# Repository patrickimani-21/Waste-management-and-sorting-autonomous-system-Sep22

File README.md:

Manage mechatronic projects

WASTE MANAGEMENT AND SORTING AUTONOMOUS SYSTEM

NAME OF TEAM MEMBERS AND THEIR ROLES

Jacob mutiso	-mechanical and trello management :	Familiar with mechanical design and project management.

Patrick gichuke	 -electrical design and simulation	:Familiar with electrical simulation design tools.

Technologies
1.	Mechanical/hardware design- AUTO DESK, PROTEUS
2.	Electrical and PCB electronic components- KI CAD, PROTEUS
3.	Programming and control- ARDUINO software
4.	Project management tool- Github and Trello apps

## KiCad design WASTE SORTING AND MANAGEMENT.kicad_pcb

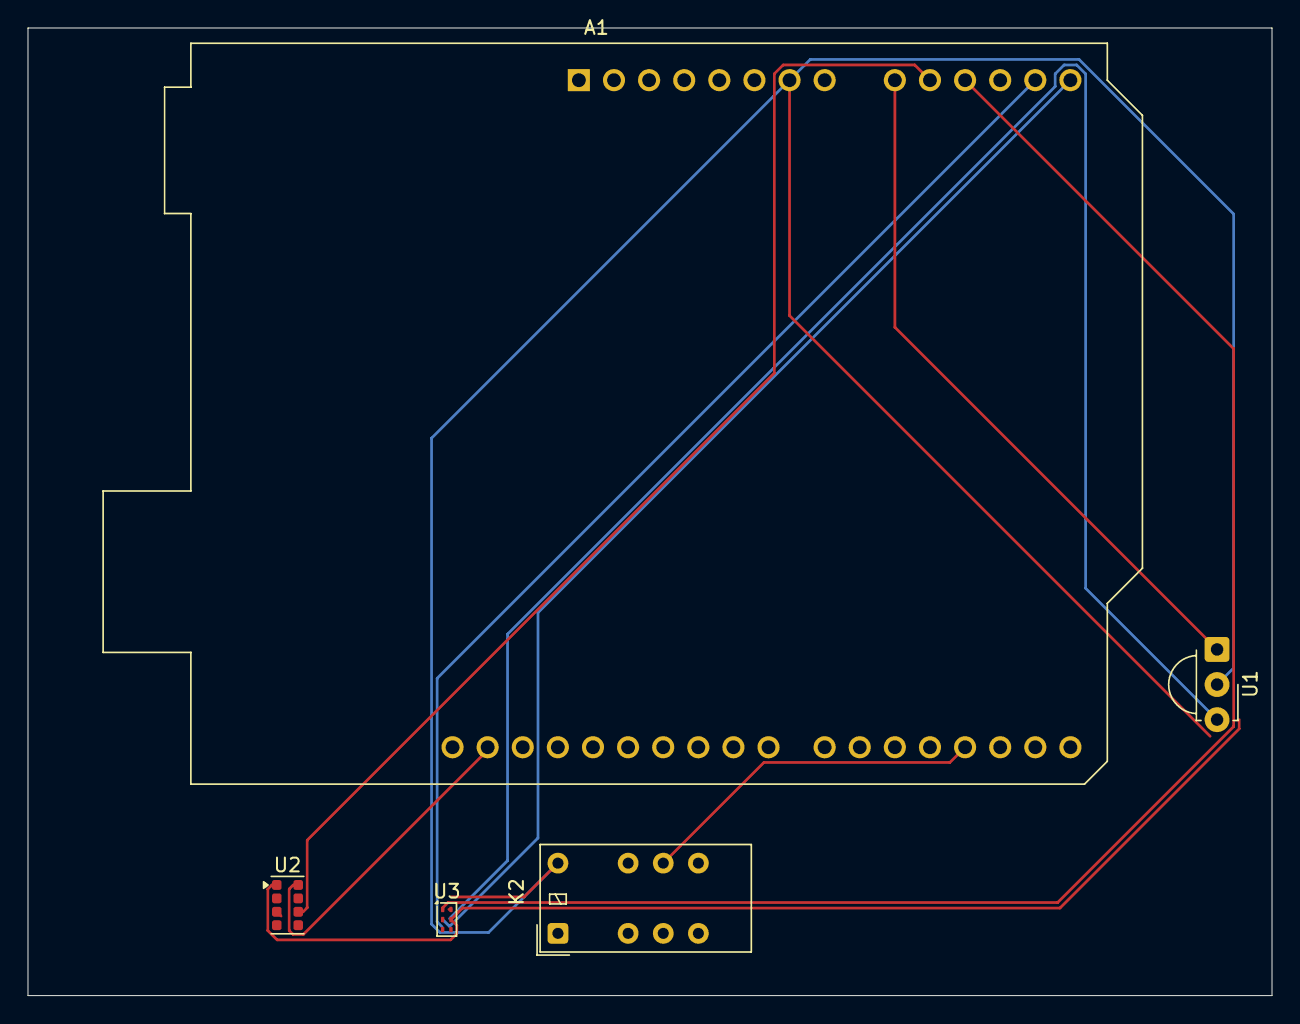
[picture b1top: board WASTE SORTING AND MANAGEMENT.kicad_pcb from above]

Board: 2 copper layers, 90.0 x 70.0 mm, 5 parts (0 on the bottom side), 11 nets.

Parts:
A1: Arduino_UNO_R3
K2: EC2-12NU; Relay_DPDT_Kemet_EC2_NU
U1: TSSP58038; Vishay_MINICAST-3Pin
U2: RPR-0521RS; Rohm_RPR-0521RS
U3: RPR-0720; Rohm_RPR-0720

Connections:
GND: A1.7 (GND), K2.12, U1.2 (GND), U2.3 (GND), U3.6 (GND)
unnamed: A1.9 (A0), U1.1 (OUT)
unnamed: A1.10 (A1), U2.6 (LDR)
unnamed: A1.11 (A2), U3.1 (VCSELA)
unnamed: A1.18 (D3), K2.9
unnamed: A1.22 (D7), K2.4
unnamed: U1.3 (Vs), U2.1 (VDD), U3.5 (VCC)
unnamed: A1.32 (SCL/A5), U2.2 (SCL)
unnamed: A1.31 (SDA/A4), U2.8 (SDA)
unnamed: A1.14 (SCL/A5), U3.2 (SCL)
unnamed: A1.13 (SDA/A4), U3.3 (SDA)
